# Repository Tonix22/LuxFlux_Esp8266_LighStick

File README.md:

# Welcome, This is Light Stick Lux Flux Project

---
## What is Lux Flux? It is an interactive juggling prop sticks that has the following features:

* Audio Rhythmic Light: For each sound peak, it can change to a different color, with up to 10 configurable color sequences.
* Motion Sensitivity: The light stick can change color when moving in clockwise or anticlockwise directions. There is also a movement gesture to turn off lights.
* Programmable Light Sequences: Light sequences can be programmed from an external andorid app or PC.
* Wi-Fi Syncing: LED sticks can be synced with Wi-Fi, so there is only a need to program one LED stick and the other one will have the same color sequence.

# WIKI

* Please visit our [WIKI](https://github.com/Tonix22/LuxFlux_Esp8266_LighStick/wiki) for more info.

----
## Developers
* Emilio Tonix : System Architecht, Tech Lead, manager,and hardware desing. 
* Ruth Solis Velasco : Ledsticks TCP Socket sync feature Developer, Android APP
* Perla Vanessa Jaime Gaytán: Auxiliar Developer and Tester
* Gisel Jimena Sanchez Salsalar: Auxiliar Developer and Tester

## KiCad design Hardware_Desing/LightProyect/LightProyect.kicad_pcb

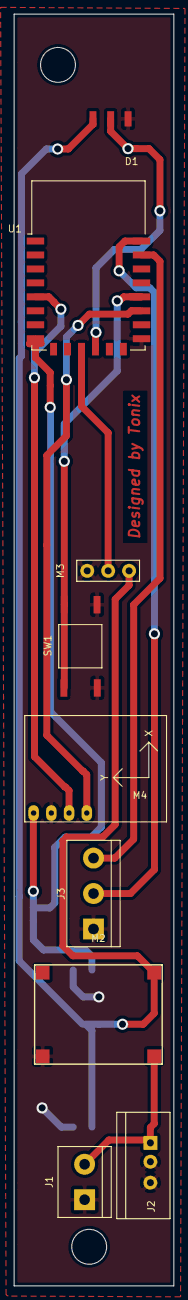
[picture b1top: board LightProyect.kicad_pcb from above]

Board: 2 copper layers, 22.9 x 182.2 mm, 10 parts (0 on the bottom side), 11 nets.

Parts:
D1: NeoPixel_THT; Neopixel
J1: Screw_Terminal_01x02; TerminalBlock_bornier-2_P5.08mm
J2: AudioJack2_SwitchT; TerminalBlock_bornier-3_P5.08mm
J3: Screw_Terminal_01x03; TerminalBlock_bornier-3_P5.08mm
M1: Regulator_x_3_3; YP8AMS1117_5v_3_3_V
M2: DC_DC_3_5_module; DC_DC_5V_3V_module
M3: AudioModule; Audio_Senso_module
M4: MPU6050_lite; GY-521
SW1: SW_Push; SW_SPST_TL3305C
U1: ESP-12E

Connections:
GND: D1.1, J1.1, J2.2, J2.3, J3.1, M1.2, M1.4, M2.2, M3.3, M4.2, SW1.2, U1.15
unnamed: D1.2, U1.12
unnamed: J3.2, U1.22
unnamed: J3.3, U1.21
unnamed: M1.1, M4.1, U1.8
unnamed: D1.3, M1.3, M2.3, M3.1
unnamed: M3.2, U1.11
unnamed: M4.3, U1.5
unnamed: M4.4, U1.17
unnamed: SW1.1, U1.18
VCC: J1.2, J2.1, M2.1

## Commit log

2020-04-04 Repo Init
2020-04-06 wifi working for AP and sta
2020-04-06 test AP
2020-06-03 neopixel logic 0 ready
2020-06-03 HIGHT WORKS
2020-06-03 rainbox neopixel
2020-06-04 Rainbow for 8 leds corrected
2020-06-05 neopixel effect created
2020-06-05 Audio light version
2020-06-08 add new message item
2020-06-08 move to cpp files
2020-06-10 Light effects ready to be done in task loop
2020-06-16 Hardware Desing Folder
2020-06-16 add imu driver into the proyect
2020-06-16 Read me added
2020-06-19 schematics changes
2020-06-19 Ruth_cambioGPIO
2020-06-22 Ruth change GPIO 5 to 10 part3
2020-06-23 PCB and Ifdef pinout
2020-06-24 Ruth GPIO 0 interrupt config
2020-06-25 light calibration task
2020-06-25 Imu Merge corrections and git ignore
2020-06-26 Corrections IMU sync
2020-06-26 Ruth Menu part1
2020-06-29 Ruth menu_ya jala
2020-06-30 linux fix
2020-06-30 Wifi configuration code
2020-06-30 Ruth menu sync functional
2020-07-01 cambio wifi a ifdef
2020-07-01 Integration imu-light
2020-07-03 PCB desing fixes
2020-07-06 heres is the commit mesage
2020-07-06 imu calib offset
2020-07-06 Code clean up and working
2020-07-06 Type correction
2020-07-06 Green light correction
2020-07-06 Post merge errors
2020-07-06 Working version with wifi, gpio ISR, IMU calibration
2020-07-07 Abort calibration if needed and menu working with ISR
2020-07-08 Menu update and solve some sync issues
2020-07-14 funcionacel
2020-07-14 imuread acel and gyro
2020-07-17 Corección de menu
2020-07-17 Hardware new pcb desing
2020-07-31 Workflow kidCad
2020-07-31 Ruth udp a tcp
2020-07-31 Working version of wifi in menu
2020-07-31 Ruth tcpintento
2020-08-01 Ruth server_init
2020-08-04 File system update
2020-08-04 Parituton table modifief
2020-08-04 update gitnore
2020-08-05 Ruth first message compare
2020-08-06 Write from flash to class with vectors
2020-08-07 Write from flash to class with linked list
2020-08-10 Reading flashing state IDLE suceed
2020-08-11 IDLE optimized by hardware and software. RGB parameter get by reference. HwTimer , Status Bits
2020-08-11 rith working
2020-08-11 Fix to move cursor to the first poistion
2020-08-12 Make an abstraction of working Menu
2020-08-12 stable version with menu and IMU working
2020-08-12 Ruth tcp client init
2020-08-13 Wifi_task vtaskdelete NULL
2020-08-20 working version
2020-08-20 sync working
2020-08-25 abstract wifi feature
2020-08-25 Comment Menu
2020-08-26 Commens, refactor and clean up
2020-08-26 Version warning
2020-08-26 sdk version protection
2020-08-26 Comments and clean up
2020-08-26 comments to clarify working place
2020-08-27 tcp_client correcciones
2020-09-02 client rx_buffer fixed
2020-09-07 tcp_client receive and parse chunks :)
2020-09-17 tcp_connect write to flash still in development
2020-09-28 file overwriting problem :) parse_chunk delete "&"
2020-11-12 Test RGB, wave to RGB converter, tcp_client_test
2020-11-18 Bug hw_timer_alarm_us FIXED :)
2020-12-08 working wihtouh wifi
2020-12-08 Wifi version update
2020-12-08 RIth Menu working
2020-12-08 tcp_client fixes, error detection and trys
2020-12-17 server_test 1 (check if it works properly)
2021-01-06 tcp_server_comunication function
2021-01-07 tcpserver read chuncks
2021-01-08 tcp_server get_pixels func
2021-01-13 free chunk memeory leak
2021-01-15 Test Linux to LUXFLUX
2021-01-20 tcpserver_test IDLE file works :)
2021-01-20 TEST folder update (tcpserver_test fixed) :)
2021-01-22 tcp_server and tcp_client finished :)
2021-02-03 Quaternion library added, pending test
2021-02-03 Quaternion library integrated
2021-02-03 junk file
2021-02-03 imu basic driver clean up
2021-02-03 IMU compiles fines
2021-02-03 code ready for first test
2021-02-04 IMU average solved
2021-02-04 temporal comments to test driver
2021-02-04 clean average and data in simple imu is tracked correctly
2021-02-04 WORKING YAW
2021-02-04 Conection Between light, memory, and IMUyawl
2021-02-04 some metada maybe usefull
2021-02-04 WORKING!!!! with filesystem hardcoded
2021-02-05 tcp_server code cleaning
2021-02-06 tcp_server final clean
2021-02-09 tcp_server include FreeRTOS_wrapper.h added
2021-02-09 tcp_server define PIXELES removed
2021-02-09 tcp_server: - rx_buffer: already out of function - tempbuff: moved to local variables
2021-02-09 tcp_server/ sync_func() var i moved near first use
2021-02-09 tcp_server: - sockaddr_in & addrLen moved - addrLen: uint to uint8_t
2021-02-09 tcp_server/ tcp_server_tack ESP_LOGE to ESP_LOGI
2021-02-09 tcp_server some comments erased
2021-02-09 tcp_server socket listen and socket banner added
2021-02-09 tcp_server var time replaced for frame_time
2021-02-09 tcp_server/tcp_server_task: comment added
2021-02-16 sdk config for windows working
2021-02-16 some fixes in APP controll
2021-02-16 remove todo
2021-02-16 update TCP_server_test
2021-02-16 gitignore
2021-02-17 Reorganización y limpieza del repo
2021-03-11 hot fix
2021-03-12 tcp Queues flash effect
2021-03-17 tcp_server lights FINISHED :)
2021-04-08 tcp_client works without queues
2021-04-08 tcp_client lights working, but with IMU colors
2021-05-28 load pattern slower tcp_light
2021-05-31 merge
2021-05-31 refactor the entire project
2021-05-31 setup android notes
2021-06-02 Queues Test
2021-06-05 Rainbow_TestingCode
2021-06-11 Backup of new design
2021-06-11 esp8266 schematics
2021-06-11 Adding leds and schematic almost done, audio pending
2021-06-21 correcciones
2021-06-29 HelloWorld :) LuxFLux App
2021-07-02 splash Screen
2021-08-05 Layout nitpicks
2021-09-30 project test
2021-09-30 test
2021-09-30 seconde test
2021-09-30 message shown
2021-09-30 Prueba holamundo, a ver si ahce push esta madre
2021-09-30 junciona?
2021-10-07 server thread and main activity code,compiles correctly. Some commented lines must be checked
2021-10-08 IP modificada
2021-10-11 folder structure
2021-10-19 try to run ktor
2021-10-26 Network checking and sockets workin
